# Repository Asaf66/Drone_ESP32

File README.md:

<div align="center">

# 🚁 ESP32 Drone Controller Board

**A Wi-Fi/Bluetooth micro-drone where the PCB *is* the airframe. Flight controller, motor drivers, sensors, and LiPo charging all sit on one 2-layer board.**

</div>

---

## ✨ Highlights

- **PCB airframe:** four arms with integrated motor mounts and slot-in landing legs, ~103 × 104 mm, so no separate frame is needed.
- **ESP32-WROOM-32E** with an on-board antenna keep-out, for Wi-Fi / BLE control.
- **Four brushed-motor channels:** logic-level MOSFETs with flyback diodes, gate resistors, and gate pull-downs on every channel.
- **Flight sensors:** a 6-axis IMU and a barometric pressure sensor for altitude hold.
- **USB-C:** programming through a CH340K USB-UART bridge with auto-reset, plus single-cell LiPo charging.
- **Manufacturing ready:** Gerbers, drill files, BOM, and CPL.

## 🧩 Block Diagram

```mermaid
flowchart LR
    USB[USB-C] --> UART[CH340K<br/>USB-UART]
    USB --> CHG[TP4056<br/>LiPo Charger]
    CHG --> BAT[(1S LiPo)]
    BAT --> LDO[AP2112K<br/>3.3V LDO]
    LDO --> MCU[ESP32-WROOM-32E]
    UART -- auto-reset --> MCU
    MCU -- SPI --> IMU[LSM6DS3<br/>6-axis IMU]
    MCU -- I2C --> BARO[LPS22HB<br/>Barometer]
    MCU -- PWM x4 --> DRV[4x SI2302<br/>MOSFET drivers]
    BAT --> DRV
    DRV --> M[4x Brushed motors]
```

## 🔧 Key Components

| Function | Part | Notes |
|---|---|---|
| MCU | **ESP32-WROOM-32E** | Wi-Fi + BLE, dual-core |
| USB-UART | **CH340K** | BC817 auto-reset / boot circuit |
| Charger | **TP4056** | 1S LiPo charging with CHG / STDBY LEDs |
| Regulator | **AP2112K-3.3** | 600 mA low-dropout 3.3 V rail |
| Power path | **AO3401A**, SS34 | P-MOSFET USB/battery switching, Schottky protection |
| Motor drivers | **SI2302** ×4 + 1N4148W ×4 | Low-side switches with flyback diodes |
| IMU | **LSM6DS3** | 3-axis accelerometer + 3-axis gyroscope (SPI) |
| Barometer | **LPS22HB** | Absolute pressure sensor for altitude (I2C) |
| Connectors | USB-C 16P, JST-PH 2P (battery), 4× JST-GH 2P (motors) | |
| Power switch | Nidec CAS-120A | SPDT slide switch |

### Motor PWM pin map (for firmware)

| Motor | Position | GPIO |
|---|---|---|
| M1 | Front right | IO13 |
| M2 | Front left | **IO12** |
| M3 | Rear left | IO26 |
| M4 | Rear right | IO27 |

## 🖼️ Gallery

| PCB Layout (F.Cu / B.Cu) | 3D View (Bottom) |
|:---:|:---:|
|  |  |

<details>
<summary><b>📐 Schematics (click to expand)</b></summary>

| Sheet | Preview |
|---|---|
| Top level |  |
| 01 – ESP32 Core & Connectivity |  |
| 02 – Power Management & LiPo |  |
| 03 – Motor Drivers & EMI Protection |  |
| 04 – Autonomous Flight Sensors |  |

</details>

## 📊 Board Stats

| Layers | Size | Thickness | Parts | Pads | Vias | Unrouted | DRC |
|:---:|:---:|:---:|:---:|:---:|:---:|:---:|:---:|
| 2 | 102.9 × 103.7 mm | 1.6 mm | 76 | 299 | 90 | **0** ✅ | **0 errors** ✅ |

## 🔁 Revision 2

Rev 2 fixes the issues found while assembling the first board:

- **USB-C:** both D+ pins (A6/B6) and both D− pins (A7/B7) are now tied, so USB works in either cable orientation.
- **CH340K:**
  - UD+/UD− corrected.
  - TX/RX now crossed to the ESP32.
  - V3 tied to VCC (required at 3.3 V).
- **Motors:**
  - Drain traces widened to 0.8 mm.
  - M2 moved from IO14 (which outputs PWM at boot) to IO12, which the gate pull-down holds low at boot.
- **Power:**
  - 10 µF input capacitor at the LDO (C18, bottom side).
  - 100 nF filter on the battery-sense ADC (C19, bottom side).
  - Footprint for an optional 100 µF bulk capacitor on the battery (C17, not fitted).
- **Mechanical:** arm slots and leg notches widened from 1.33 mm to 1.80 mm, so the 1.6 mm landing legs fit.
- **DRC:** board-edge clearance check re-enabled. A custom rule exempts only the joint solder pads.

All top-side footprints are unchanged from Rev 1, so the original paste stencil can be reused. Full review: [`docs/Rev2_Design_Review.md`](docs/Rev2_Design_Review.md).

## 📁 Repository Structure

```
Drone_ESP32/
├── Drone_ESP32.kicad_pro / .kicad_sch / .kicad_pcb   # KiCad project (top level + PCB)
├── Drone_ESP32.kicad_dru        # Custom DRC rules
├── ESP32_Core.kicad_sch         # Sheet 01 – MCU, USB-UART, auto-reset
├── Power_Management.kicad_sch   # Sheet 02 – USB-C, LiPo charger, LDO, power switch
├── Motor_Drivers.kicad_sch      # Sheet 03 – 4x MOSFET motor drivers
├── Sensors_Suite.kicad_sch      # Sheet 04 – IMU + barometer
├── Drone_Custom.3dshapes/       # 3D model for the USB-C connector
├── Gerbers/                     # Gerbers, drill files, JLCPCB zip
├── BOM.csv · CPL.csv            # Bill of materials and placement (JLCPCB format)
├── docs/                        # Design review
├── DATA SHEET/                  # Component datasheets
└── images/                      # Renders & schematic exports
```

## 🏭 Manufacturing

**Bare PCB:**
1. Upload `Gerbers/Drone_ESP32_JLCPCB.zip` to JLCPCB.
2. Order with these options: 2 layers, FR-4, 1.6 mm, HASL.

**Assembly (optional):**
1. Enable **PCB Assembly** and upload `BOM.csv` and `CPL.csv`.
2. Review part placement and rotation in the preview before ordering.
3. C18 and C19 are on the bottom side, and C17 is not fitted.

---

<div align="center">

Designed by **Asaf Aharon** · [GitHub](https://github.com/Asaf66) · [LinkedIn](https://linkedin.com/in/asaf-aharon-015595231)

</div>

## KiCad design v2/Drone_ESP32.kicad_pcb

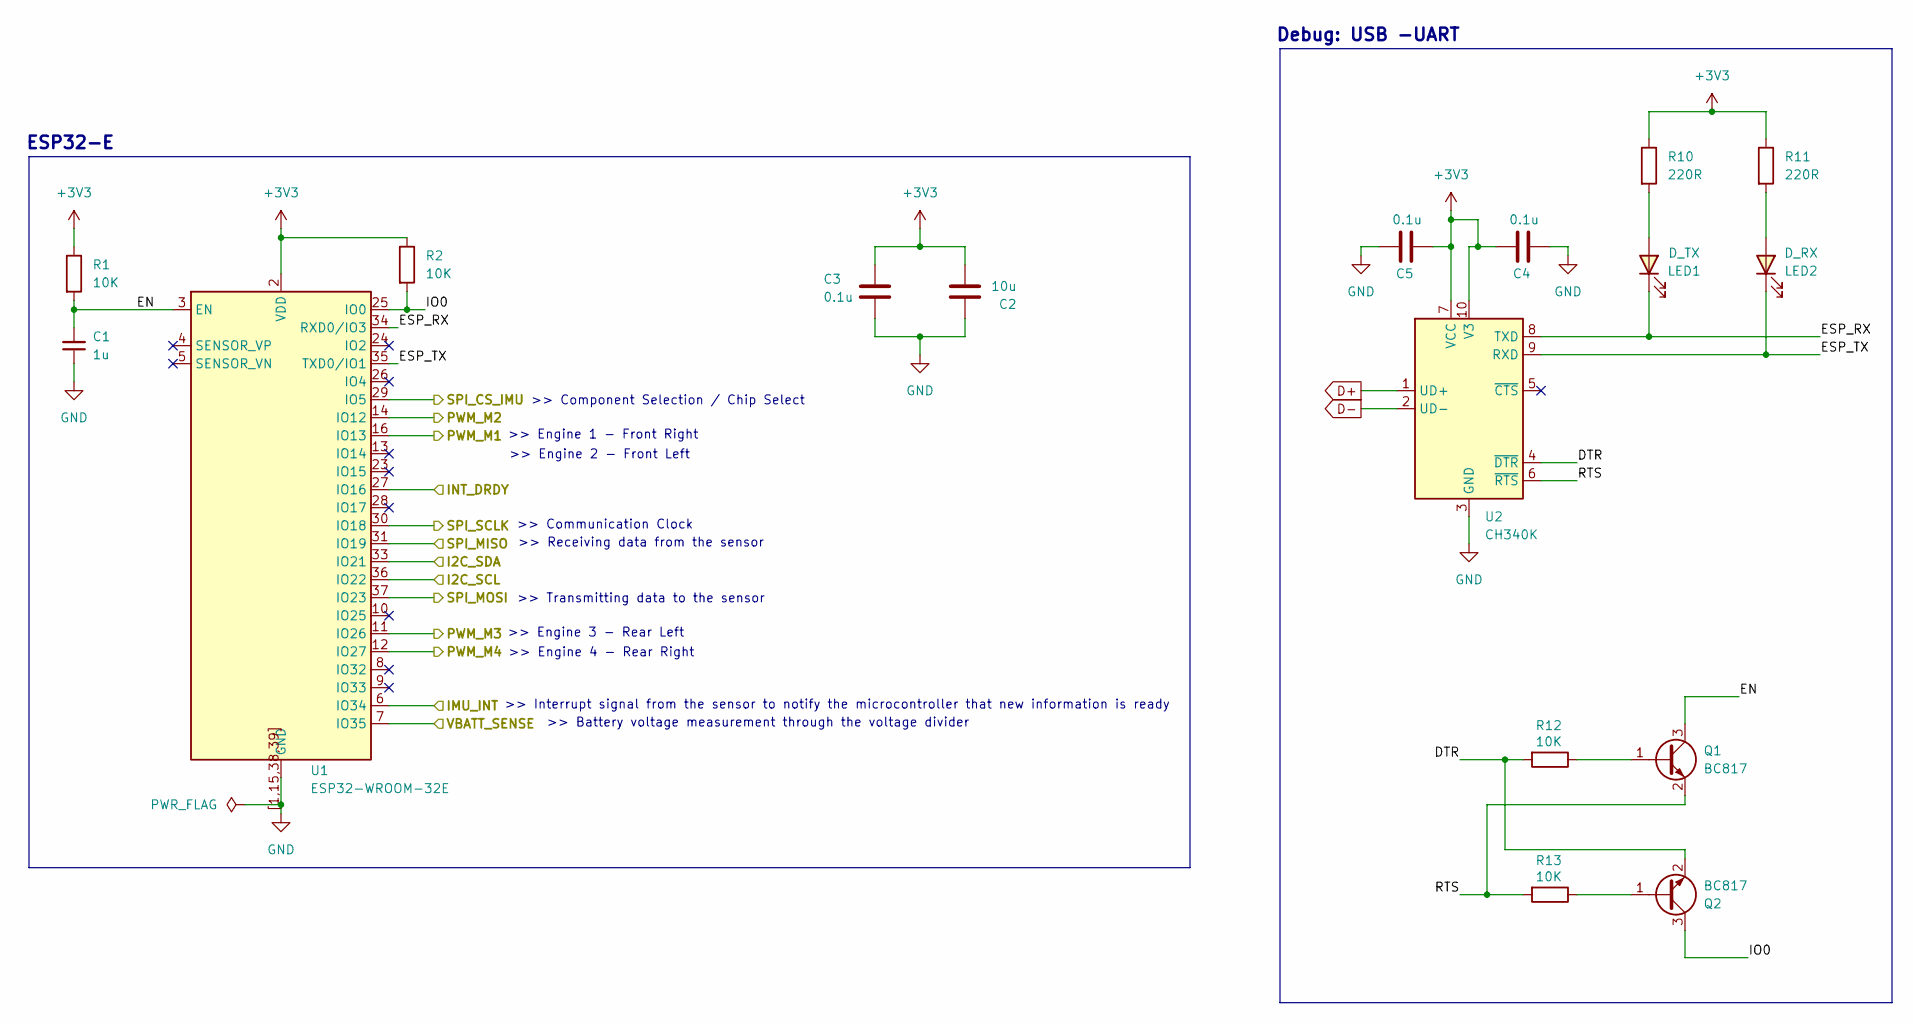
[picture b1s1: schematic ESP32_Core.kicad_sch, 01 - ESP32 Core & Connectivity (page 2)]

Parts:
C1: 1u; C_0603_1608Metric
C2: 10u; C_0603_1608Metric
C3, C4, C5: 0.1u; C_0603_1608Metric
LED1: D_TX; LED_0603_1608Metric
LED2: D_RX; LED_0603_1608Metric
Q1, Q2: BC817; SOT-23
R1, R2, R12, R13: 10K; R_0805_2012Metric
R10, R11: 220R; R_0805_2012Metric
U1: ESP32-WROOM-32E
U2: CH340K; SSOP-10-1EP_3.9x4.9mm_P1mm_EP2.1x3.3mm

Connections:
+3V3: C2.1, C3.2, C4.1, C5.2, R1.1, R2.1, R10.1, R11.1, U1.2 (VDD), U2.7 (VCC), U2.10 (V3); also elsewhere on the board
/01 - ESP32 Core & Connectivity (page 2)/DTR: Q2.2 (E), R12.2, U2.4 (~DTR)
/01 - ESP32 Core & Connectivity (page 2)/EN: C1.2, Q1.3 (C), R1.2, U1.3 (EN)
/01 - ESP32 Core & Connectivity (page 2)/ESP_RX: LED1.1 (K), U1.34 (RXD0/IO3), U2.8 (TXD)
/01 - ESP32 Core & Connectivity (page 2)/ESP_TX: LED2.1 (K), U1.35 (TXD0/IO1), U2.9 (RXD)
/01 - ESP32 Core & Connectivity (page 2)/I2C_SCL: U1.36 (IO22); also elsewhere on the board
/01 - ESP32 Core & Connectivity (page 2)/I2C_SDA: U1.33 (IO21); also elsewhere on the board
/01 - ESP32 Core & Connectivity (page 2)/IMU_INT: U1.6 (IO34); also elsewhere on the board
/01 - ESP32 Core & Connectivity (page 2)/INT_DRDY: U1.27 (IO16); also elsewhere on the board
/01 - ESP32 Core & Connectivity (page 2)/IO0: Q2.3 (C), R2.2, U1.25 (IO0)
/01 - ESP32 Core & Connectivity (page 2)/PWM_M1: U1.16 (IO13); also elsewhere on the board
/01 - ESP32 Core & Connectivity (page 2)/PWM_M2: U1.14 (IO12); also elsewhere on the board
/01 - ESP32 Core & Connectivity (page 2)/PWM_M3: U1.11 (IO26); also elsewhere on the board
/01 - ESP32 Core & Connectivity (page 2)/PWM_M4: U1.12 (IO27); also elsewhere on the board
/01 - ESP32 Core & Connectivity (page 2)/RTS: Q1.2 (E), R13.2, U2.6 (~RTS)
/01 - ESP32 Core & Connectivity (page 2)/SPI_CS_IMU: U1.29 (IO5); also elsewhere on the board
/01 - ESP32 Core & Connectivity (page 2)/SPI_MISO: U1.31 (IO19); also elsewhere on the board
/01 - ESP32 Core & Connectivity (page 2)/SPI_MOSI: U1.37 (IO23); also elsewhere on the board
/01 - ESP32 Core & Connectivity (page 2)/SPI_SCLK: U1.30 (IO18); also elsewhere on the board
/01 - ESP32 Core & Connectivity (page 2)/VBATT_SENSE: U1.7 (IO35); also elsewhere on the board
D+: U2.1 (UD-); also elsewhere on the board
D-: U2.2 (UD+); also elsewhere on the board
GND: C1.1, C2.2, C3.1, C4.2, C5.1, U1.1 (GND), U1.15 (GND), U1.38 (GND), U1.39 (GND), U1.[1,15,38,39] (GND), U2.3 (GND), U2.11 (GND); also elsewhere on the board
unnamed: LED1.2 (A), R10.2
unnamed: LED2.2 (A), R11.2
unnamed: Q1.1 (B), R12.1
unnamed: Q2.1 (B), R13.1

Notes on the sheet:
>> Interrupt signal from the sensor to notify the microcontroller that new information is ready
>> Communication Clock
Debug: USB -UART
>> Engine 2 - Front Left
ESP32-E
>> Engine 3 - Rear Left
>> Engine 1 - Front Right
>> Receiving data from the sensor
>> Component Selection / Chip Select
>> Engine 4 - Rear Right
>> Transmitting data to the sensor
>> Battery voltage measurement through the voltage divider

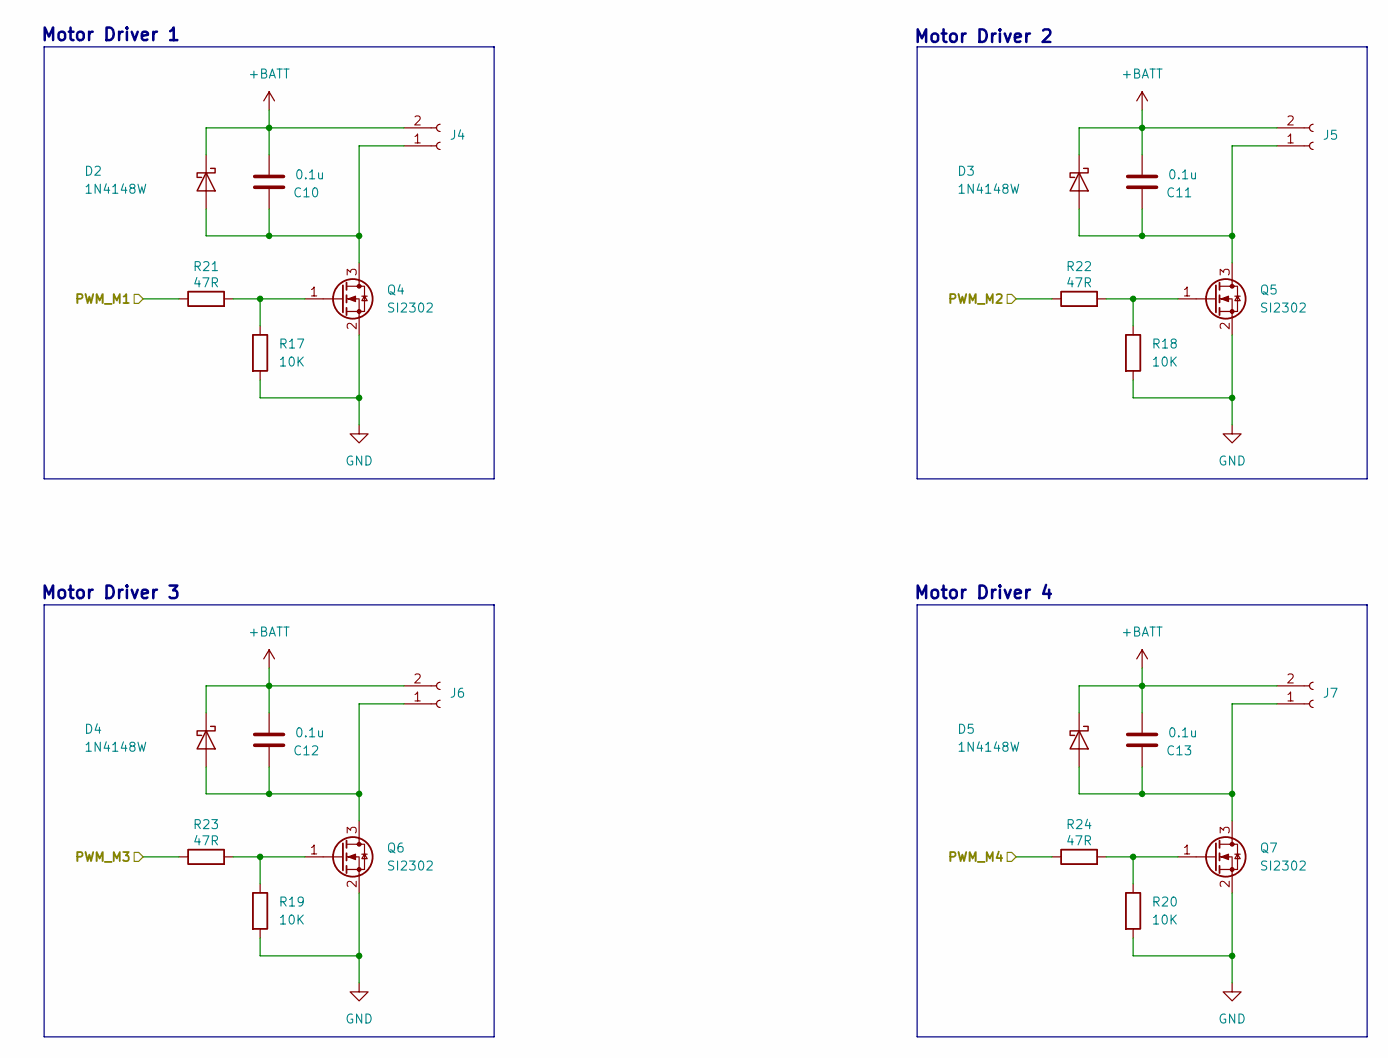
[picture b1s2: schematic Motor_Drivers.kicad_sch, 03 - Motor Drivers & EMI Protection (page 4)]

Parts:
C10, C11, C12, C13: 0.1u; C_0603_1608Metric
D2, D3, D4, D5: 1N4148W; Nexperia_CFP3_SOD-123W
J4, J5, J6, J7: Conn_01x02_Socket; JST_GH_SM02B-GHS-TB_1x02-1MP_P1.25mm_Horizontal
Q4, Q5, Q6, Q7: SI2302; SOT-23
R17, R18, R19, R20: 10K; R_0805_2012Metric
R21, R22, R23, R24: 47R; R_0805_2012Metric

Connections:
+BATT: C10.1, C11.1, C12.1, C13.1, D2.1 (K), D3.1 (K), D4.1 (K), D5.1 (K), J4.2, J5.2, J6.2, J7.2; also elsewhere on the board
/01 - ESP32 Core & Connectivity (page 2)/PWM_M1: R21.1; also elsewhere on the board
/01 - ESP32 Core & Connectivity (page 2)/PWM_M2: R22.1; also elsewhere on the board
/01 - ESP32 Core & Connectivity (page 2)/PWM_M3: R23.1; also elsewhere on the board
/01 - ESP32 Core & Connectivity (page 2)/PWM_M4: R24.1; also elsewhere on the board
GND: Q4.2 (S), Q5.2 (S), Q6.2 (S), Q7.2 (S), R17.2, R18.2, R19.2, R20.2; also elsewhere on the board
unnamed: C10.2, D2.2 (A), J4.1, Q4.3 (D)
unnamed: C11.2, D3.2 (A), J5.1, Q5.3 (D)
unnamed: C12.2, D4.2 (A), J6.1, Q6.3 (D)
unnamed: C13.2, D5.2 (A), J7.1, Q7.3 (D)
unnamed: Q4.1 (G), R17.1, R21.2
unnamed: Q5.1 (G), R18.1, R22.2
unnamed: Q6.1 (G), R19.1, R23.2
unnamed: Q7.1 (G), R20.1, R24.2

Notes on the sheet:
Motor Driver 4
Motor Driver 2
Motor Driver 1
Motor Driver 3

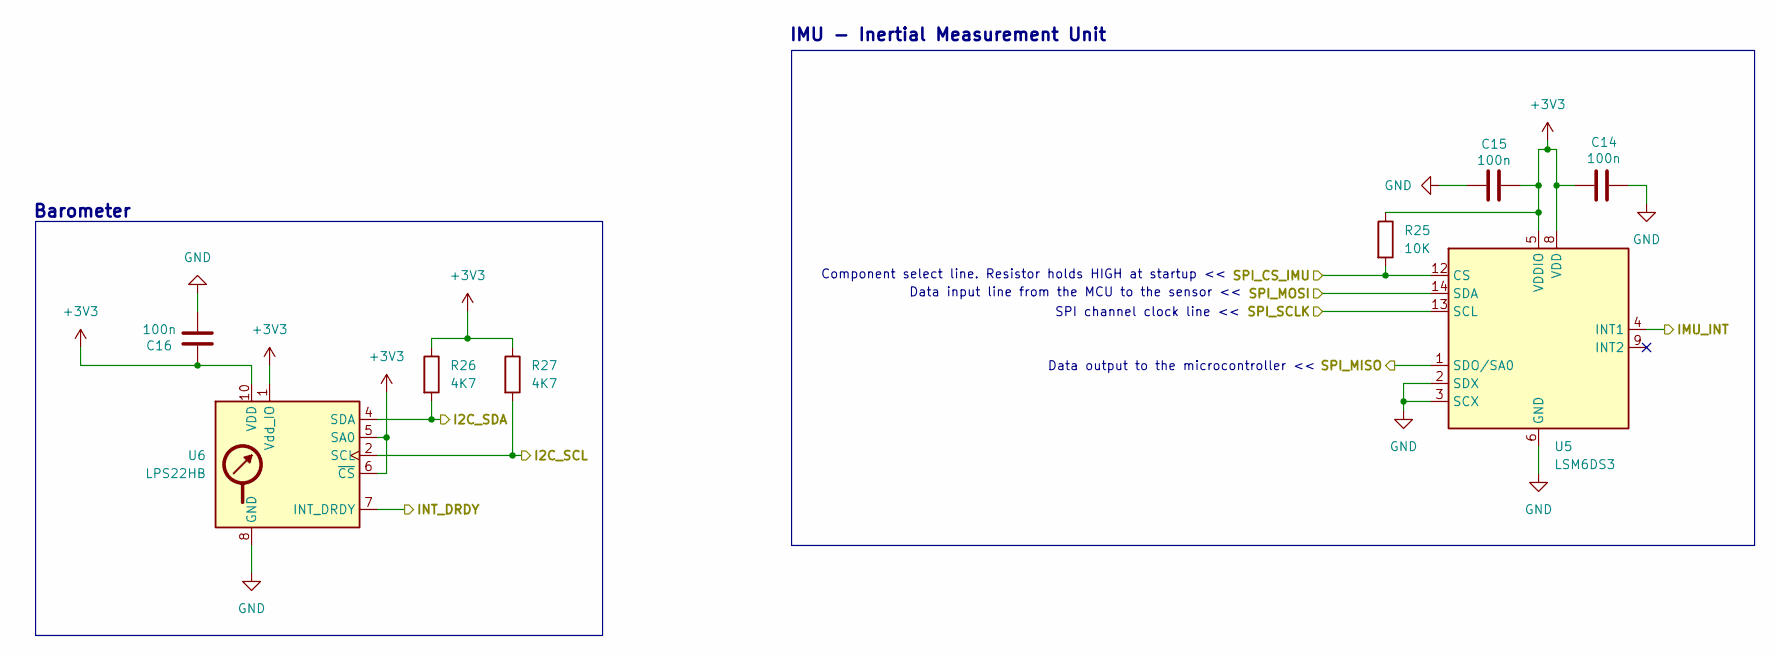
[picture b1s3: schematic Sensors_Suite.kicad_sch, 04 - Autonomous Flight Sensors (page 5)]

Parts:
C14, C15, C16: 100n; C_0603_1608Metric
R25: 10K; R_0805_2012Metric
R26, R27: 4K7; R_0805_2012Metric
U5: LSM6DS3; LGA-14_3x2.5mm_P0.5mm_LayoutBorder3x4y
U6: LPS22HB; ST_HLGA-10_2x2mm_P0.5mm_LayoutBorder3x2y

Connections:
+3V3: C14.1, C15.2, C16.1, R25.1, R26.1, R27.1, U5.5 (VDDIO), U5.8 (VDD), U6.1 (Vdd_IO), U6.5 (SA0), U6.6 (~CS), U6.10 (VDD); also elsewhere on the board
/01 - ESP32 Core & Connectivity (page 2)/I2C_SCL: R27.2, U6.2 (SCL); also elsewhere on the board
/01 - ESP32 Core & Connectivity (page 2)/I2C_SDA: R26.2, U6.4 (SDA); also elsewhere on the board
/01 - ESP32 Core & Connectivity (page 2)/IMU_INT: U5.4 (INT1); also elsewhere on the board
/01 - ESP32 Core & Connectivity (page 2)/INT_DRDY: U6.7 (INT_DRDY); also elsewhere on the board
/01 - ESP32 Core & Connectivity (page 2)/SPI_CS_IMU: R25.2, U5.12 (CS); also elsewhere on the board
/01 - ESP32 Core & Connectivity (page 2)/SPI_MISO: U5.1 (SDO/SA0); also elsewhere on the board
/01 - ESP32 Core & Connectivity (page 2)/SPI_MOSI: U5.14 (SDA); also elsewhere on the board
/01 - ESP32 Core & Connectivity (page 2)/SPI_SCLK: U5.13 (SCL); also elsewhere on the board
GND: C14.2, C15.1, C16.2, U5.2 (SDX), U5.3 (SCX), U5.6 (GND), U5.7 (GND), U6.3 (GND), U6.8 (GND), U6.9 (GND); also elsewhere on the board

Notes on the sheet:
Data input line from the MCU to the sensor <<
Component select line. Resistor holds HIGH at startup <<
SPI channel clock line <<
Data output to the microcontroller <<
IMU - Inertial Measurement Unit
Barometer

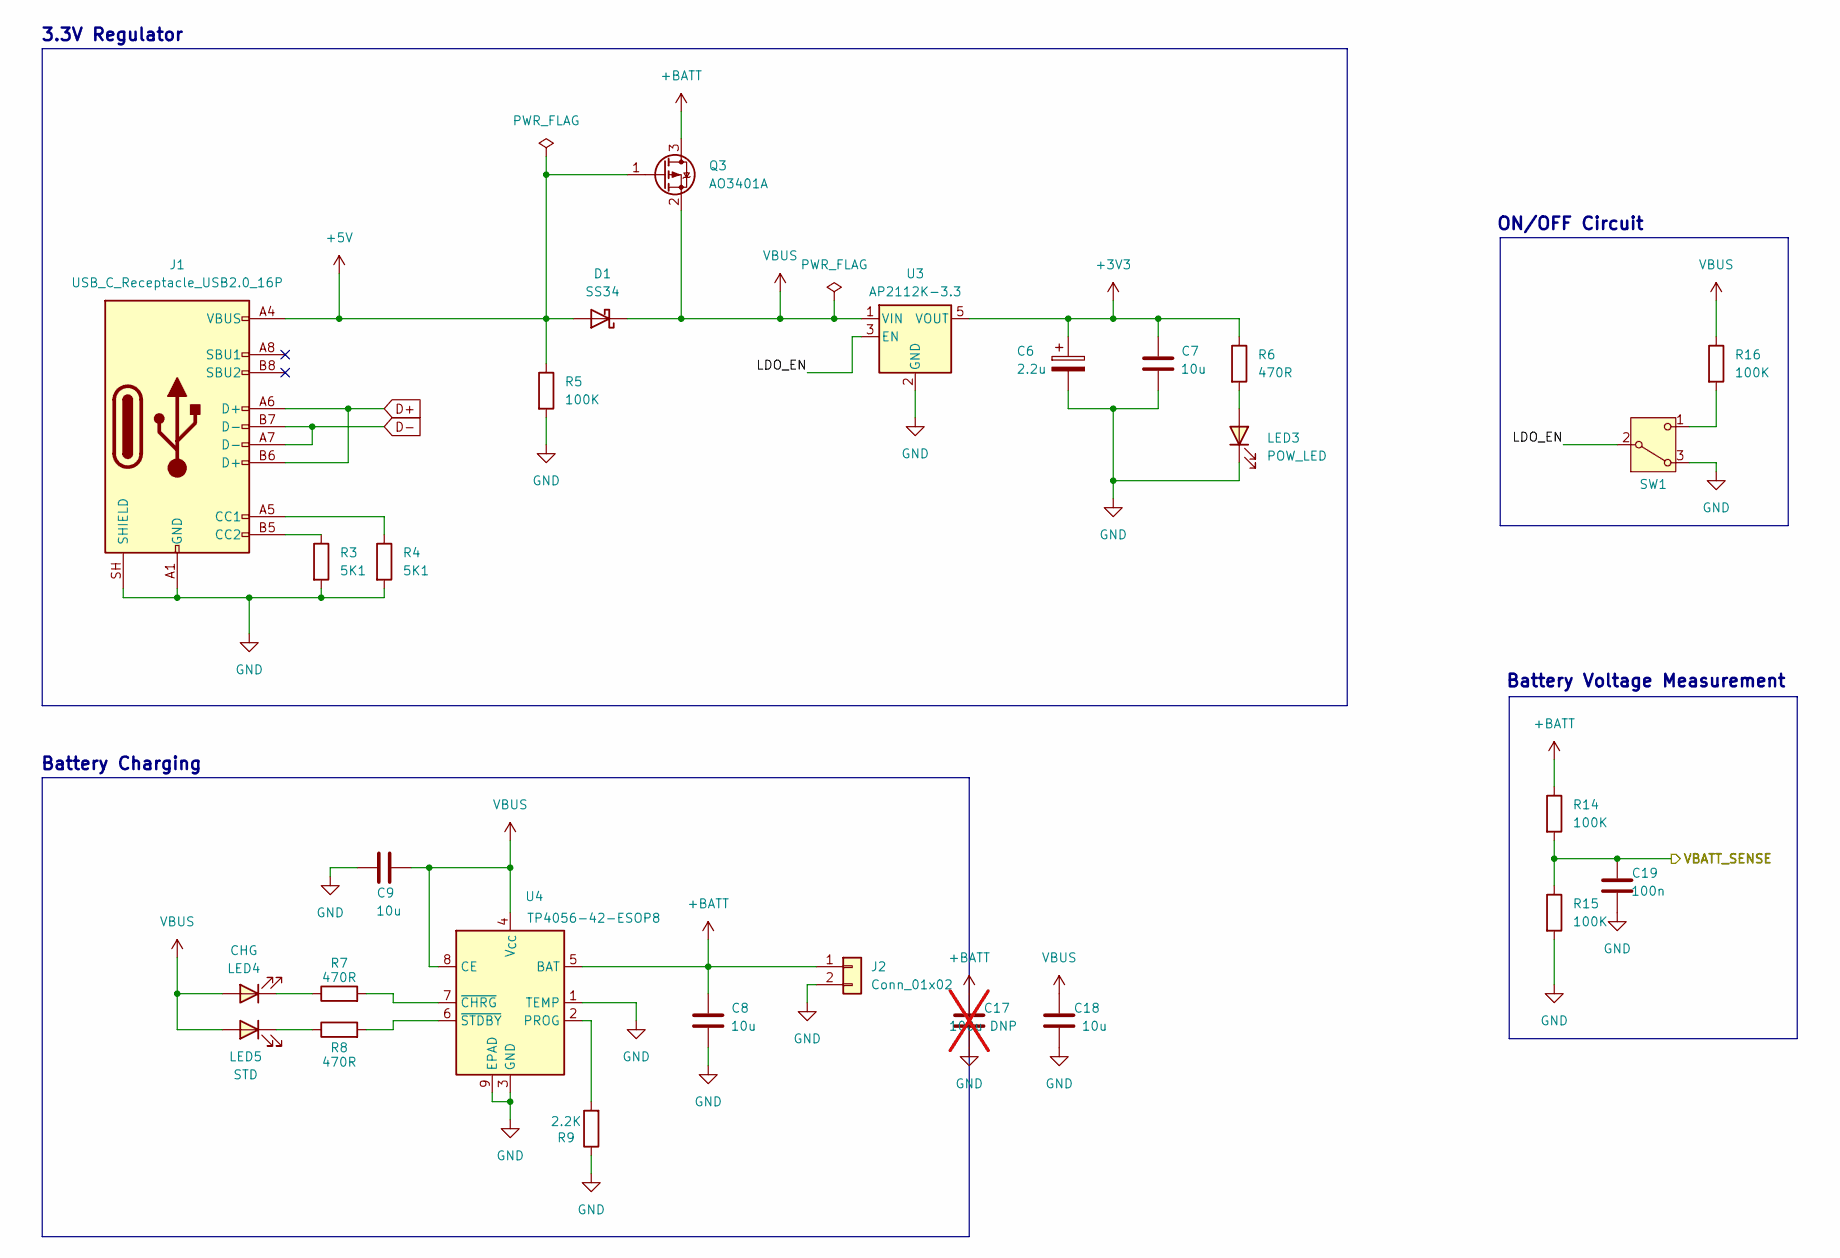
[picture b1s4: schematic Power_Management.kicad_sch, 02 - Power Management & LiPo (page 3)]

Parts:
C6: 2.2u; C_0603_1608Metric
C7, C8, C9, C18: 10u; C_0603_1608Metric
C17: 100u DNP; C_1210_3225Metric; not fitted
C19: 100n; C_0603_1608Metric
D1: SS34; D_SMA
J1: USB_C_Receptacle_USB2.0_16P; USB_C_Receptacle_HRO_TYPE-C-31-M-12
J2: Conn_01x02; JST_PH_B2B-PH-K_1x02_P2.00mm_Vertical
LED3: POW_LED; LED_0603_1608Metric
LED4: CHG; LED_0603_1608Metric
LED5: STD; LED_0603_1608Metric
Q3: AO3401A; SOT-23
R3, R4: 5K1; R_0805_2012Metric
R5, R14, R15, R16: 100K; R_0805_2012Metric
R6, R7, R8: 470R; R_0805_2012Metric
R9: 2.2K; R_0805_2012Metric
SW1: CAS-120A1; Nidec_Copal_CAS-120A
U3: AP2112K-3.3; SOT-23-5
U4: TP4056-42-ESOP8; SOIC-8-1EP_3.9x4.9mm_P1.27mm_EP2.41x3.3mm_ThermalVias

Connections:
+3V3: C6.1, C7.1, R6.1, U3.5 (VOUT); also elsewhere on the board
+5V: D1.2 (A), J1.A4 (VBUS), J1.A9 (VBUS), J1.B4 (VBUS), J1.B9 (VBUS), Q3.1 (G), R5.1
+BATT: C8.1, C17.1, J2.1, Q3.3 (D), R14.1, U4.5 (BAT); also elsewhere on the board
/01 - ESP32 Core & Connectivity (page 2)/VBATT_SENSE: C19.1, R14.2, R15.1; also elsewhere on the board
/02 - Power Management & LiPo/LDO_EN: SW1.2 (B), U3.3 (EN)
D+: J1.A6 (D+), J1.B6 (D+); also elsewhere on the board
D-: J1.A7 (D-), J1.B7 (D-); also elsewhere on the board
GND: C6.2, C7.2, C8.2, C9.2, C17.2, C18.2, C19.2, J1.A1 (GND), J1.A12 (GND), J1.B1 (GND), J1.B12 (GND), J1.SH (SHIELD), J2.2, LED3.1 (K), R3.2, R4.2, R5.2, R9.1, R15.2, SW1.3 (A), U3.2 (GND), U4.1 (TEMP), U4.3 (GND), U4.9 (EPAD); also elsewhere on the board
unnamed: J1.A5 (CC1), R4.1
unnamed: J1.B5 (CC2), R3.1
unnamed: LED3.2 (A), R6.2
unnamed: LED4.1 (K), R7.1
unnamed: LED5.1 (K), R8.1
unnamed: R16.2, SW1.1 (C)
unnamed: R9.2, U4.2 (PROG)
unnamed: R7.2, U4.7 (~CHRG)
unnamed: R8.2, U4.6 (~STDBY)
VBUS: C9.1, C18.1, D1.1 (K), LED4.2 (A), LED5.2 (A), Q3.2 (S), R16.1, U3.1 (VIN), U4.4 (V_{CC}), U4.8 (CE)

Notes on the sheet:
ON/OFF Circuit
Battery Charging
Battery Voltage Measurement
3.3V Regulator

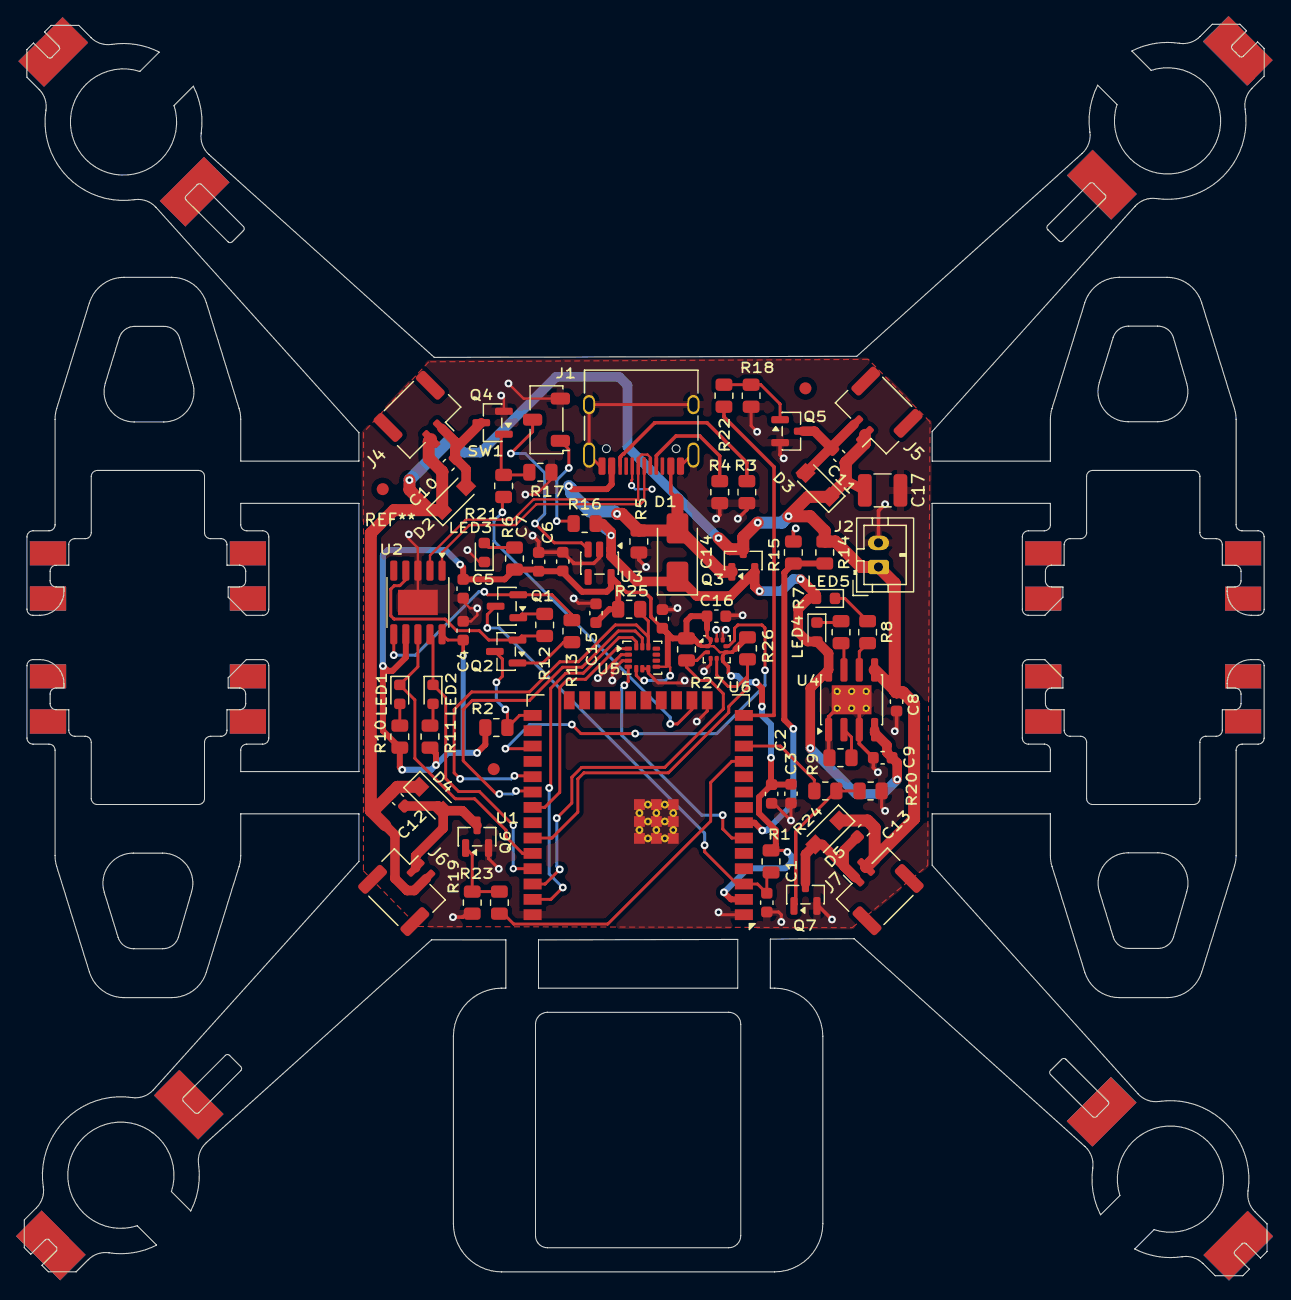
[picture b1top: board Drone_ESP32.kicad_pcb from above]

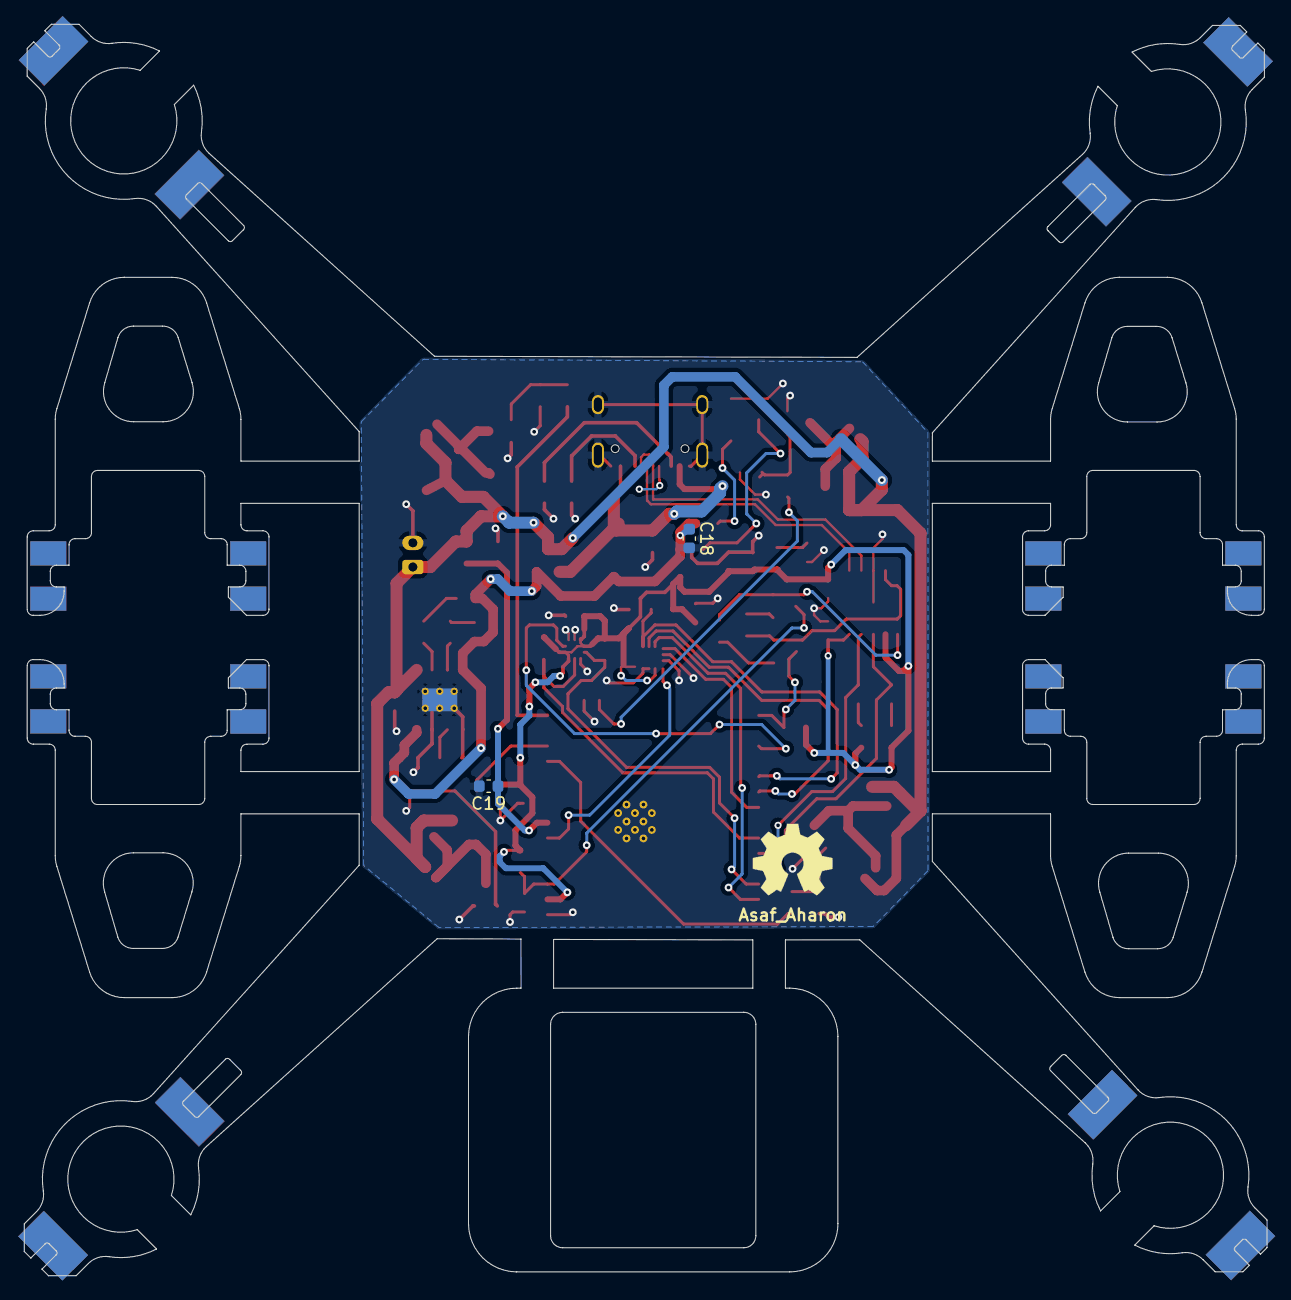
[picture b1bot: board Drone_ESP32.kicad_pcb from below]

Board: 2 copper layers, 102.9 x 103.7 mm, 76 parts (2 on the bottom side), 48 nets.

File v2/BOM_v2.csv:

Comment,Designator,Footprint,JLCPCB Part #（optional）,Quantity
1u,C1,C_0603_1608Metric,C15849,1
100u DNP (not fitted),C17,C_1210_3225Metric,,0
10u,"C2, C7, C8, C9, C18",C_0603_1608Metric,C19702,5
0.1u,"C3, C4, C5, C10, C11, C12, C13",C_0603_1608Metric,C14663,7
2.2u,C6,C_0603_1608Metric,C23630,1
100n,"C14, C15, C16, C19",C_0603_1608Metric,C14663,4
SS34,D1,D_SMA,C8678,1
1N4148W,"D2, D3, D4, D5",Nexperia_CFP3_SOD-123W,C81598,4
USB_C_Receptacle_USB2.0_16P,J1,USB_C_Receptacle_HRO_TYPE-C-31-M-12,C393939,1
JST PH 2P vertical THT (B2B-PH-K-S),J2,JST_PH_B2B-PH-K_1x02_P2.00mm_Vertical,,1
Conn_01x02_Socket,"J4, J5, J6, J7",JST_GH_SM02B-GHS-TB_1x02-1MP_P1.25mm_Horizontal,C54582897,4
D_TX,LED1,LED_0603_1608Metric,C2290,1
D_RX,LED2,LED_0603_1608Metric,C2290,1
POW_LED,LED3,LED_0603_1608Metric,C2290,1
CHG,LED4,LED_0603_1608Metric,C118330,1
STD,LED5,LED_0603_1608Metric,C965804,1
BC817,"Q1, Q2",SOT-23,C475629,2
AO3401A,Q3,SOT-23,C15127,1
SI2302 (VBsemi SI2302DS-T1-GE3-VB),"Q4, Q5, Q6, Q7",SOT-23,C558245,4
10K,"R1, R2, R12, R13, R17, R18, R19, R20, R25",R_0805_2012Metric,C17414,9
5K1,"R3, R4",R_0805_2012Metric,C27834,2
100K,"R5, R14, R15, R16",R_0805_2012Metric,C149504,4
470R,"R6, R7, R8",R_0805_2012Metric,C17710,3
2.2K,R9,R_0805_2012Metric,C17520,1
220R,"R10, R11",R_0805_2012Metric,C17557,2
47R,"R21, R22, R23, R24",R_0805_2012Metric,C17714,4
4K7,"R26, R27",R_0805_2012Metric,C17673,2
Nidec CAS-120A (SPDT slide),SW1,Nidec_Copal_CAS-120A,C5962834,1
ESP32-WROOM-32E,U1,ESP32-WROOM-32E,C701342,1
CH340K,U2,SSOP-10-1EP_3.9x4.9mm_P1mm_EP2.1x3.3mm,C18208922,1
AP2112K-3.3,U3,SOT-23-5,C23380830,1
TP4056-42-ESOP8,U4,SOIC-8-1EP_3.9x4.9mm_P1.27mm_EP2.41x3.3mm_ThermalVias,C16581,1
LSM6DS3,U5,LGA-14_3x2.5mm_P0.5mm_LayoutBorder3x4y,C967633,1
LPS22HB,U6,ST_HLGA-10_2x2mm_P0.5mm_LayoutBorder3x2y,C94049,1
